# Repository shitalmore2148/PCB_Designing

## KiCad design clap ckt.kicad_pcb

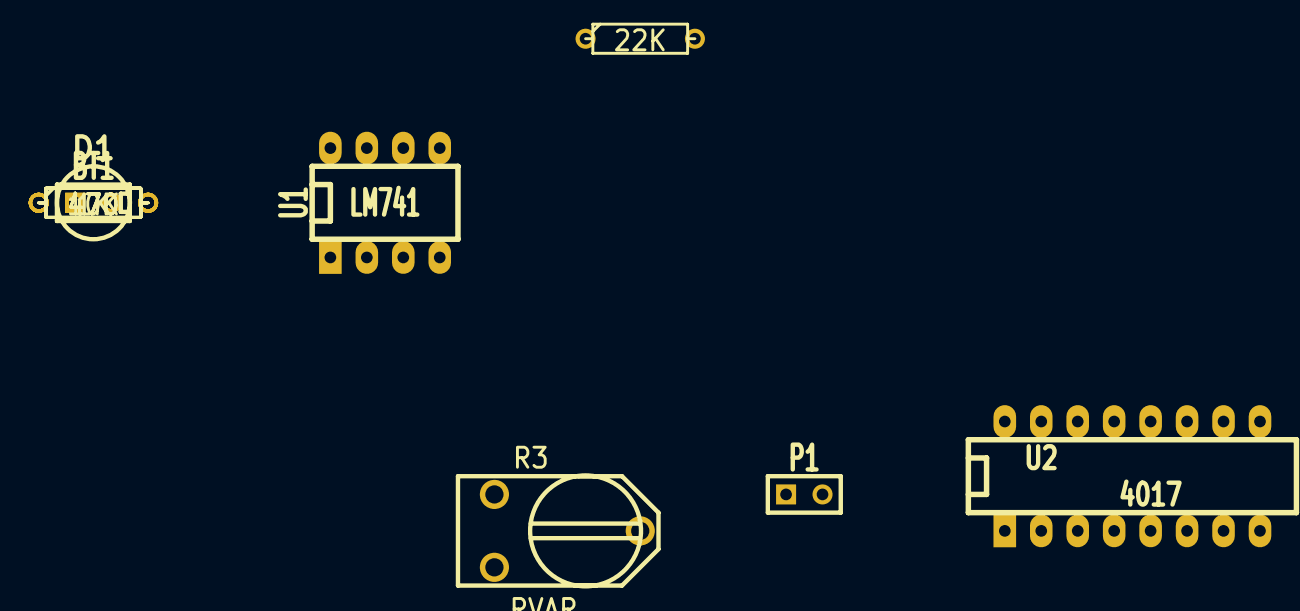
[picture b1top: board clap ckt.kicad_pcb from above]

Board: 2 copper layers, 11 parts (0 on the bottom side), 10 nets, no tracks yet.

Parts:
BT1: BATTERY; SIL-2
D1: LED; LEDV
P1: CONN_2; SIL-2
R1: 22K; R3
R2: 1K; R3
R3: RVAR; RV2X4
R4, R6: 470; R3
R5: 10K; R3
U1: LM741; DIP-8__300_ELL
U2: 4017; DIP-16__300_ELL

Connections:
unnamed: R3.2, R4.1
unnamed: BT1.2, D1.2, P1.2, R4.2, R5.2, U1.4
unnamed: D1.1, R6.2
unnamed: R2.2, R3.1, U1.3
unnamed: P1.1, R1.2, U1.2
unnamed: R6.1, U2.3
unnamed: U2.4, U2.15
unnamed: U2.12, U2.13
unnamed: BT1.1, R1.1, R2.1, U1.7
unnamed: R5.1, U1.6, U2.14
